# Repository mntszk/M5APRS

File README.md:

# M5APRS

M5Stack Basic GPS APRS tracker/receiver (1200bps AFSK)

[English](README.en.md) | 日本語

M5Stack Basic V2.6 で、GPS の位置を APRS パケットにして 1200bps AFSK で無線機へ送り、無線機で受信した APRS をデコードして画面に表示するアマチュア無線用のソフトです。個人の趣味のプロジェクトで、M5Stack 社とは関係ありません。

## かんたん書き込み (ビルド済みファイル)
Arduino IDE がなくても、ブラウザだけで書き込めます。

1. [Releases](https://github.com/mntszk/M5APRS/releases) から、最新の版の `M5APRS-x.y.z.bin` をダウンロードする (`x.y.z` は版の番号)
2. M5Stack Basic を USB ケーブルでパソコンにつなぐ
3. Chrome か Edge で、Espressif の書き込みツール [ESP Tool (esptool-js)](https://espressif.github.io/esptool-js/) を開く
4. 「Program」の欄で Baudrate を `921600` にして「Connect」を押し、出てきた一覧から M5Stack のポートを選ぶ
5. 「Flash Address」を **`0x0`** にして、1 のファイルを選び、「Program」を押す
6. 書き込みが終わったら、M5Stack のリセット (電源) ボタンを押して起動する
7. 続いて、下の「[使い方](#使い方)」の 4 (microSD の config.txt) に進む

- ポートが一覧に出ないときは、USB 変換チップのドライバー (M5Stack Basic V2.6 は CH9102) を入れてください
- 「Erase Flash」は押さないでください。押すと、本体に保存した設定 (シンボル、SSID、音量など) も消えます。押さなければ、版を上げても設定は残ります
- コマンドで書き込む場合: `esptool.py --chip esp32 --port <ポート> --baud 921600 write_flash 0x0 M5APRS-x.y.z.bin`

## 主な機能
- GPS (NMEA) の位置から、APRS の位置レポート (非圧縮形式) を作って送信 (A長押しで1パケット、または自動送信)
- ビーコンの自動送信: オフ / Ackのみ / 1〜60分ごと / フレックス (設定メニューで選択。電源を切っても保持)。他局の送信中は止むまで待つ
- フレックス: 速度と曲がり方で送信の間隔を変える。八重洲・ケンウッドの無線機のスマートビーコニングと同じ方式・同じ項目で、値は config.txt に書く
- 送信時に PTT を自動で ON/OFF (GPIO5 → トランジスタ)。PTT の最大時間は 10 秒
- 1200bps AFSK (Bell 202) の受信・デコード。非圧縮形式、圧縮形式、Mic-E の位置や、メッセージなどを受信一覧に表示
- メッセージ: 自分宛てのメッセージと一斉通知の受信、Ackの自動返送、メッセージの送信 (Ackが来るまで送り直し)。宛先は受信した局から、本文は定型文から選ぶ。CardKB2 をつなげば文字も入力できる
- 受信音: パケット・自局の折り返し・Ack・メッセージで音を分けて鳴らす (音量はモニター音とは別に設定)
- 記録の消去: 受信一覧・WX局・メッセージ・レーダーの局を、設定メニューから一覧ごと (またはすべて) 消せる (確認つき)
- WX(気象)画面: 気象データを含むパケットを受信した局 (最大8局) の気温・湿度・気圧・風・雨量を一覧と詳細で表示
- 受信状態の画面: 信号あり / データ受信中 / 受信OK / CRC不良、入力レベル、MARK/SPACE のトーン強度と比 (直近に受けた局の比も)、受信OK・CRC不良・雑音の件数
- 位置の取得元を手動で選択: GPS / 最後の位置 / 固定位置 (config.txt に最大8件)
- 送信音のモニター (内蔵スピーカー、5段階)
- 調整トーン: 設定メニューから、PTT付きで連続トーン (1200Hz / 2200Hz / 交互) を出して、減衰回路や送信レベルを調整できる (ダミーロード前提)
- シリアルモニタ (115200bps) への診断出力: PTTのタイミング、送受信パケット、受信の状態、定期の状態
- microSD に受信ログ (CSV) と動作ログを保存
- コールサインなど局ごとの設定は microSD の `config.txt` に書く (ビルドのときに書き換えるファイルはない)
- シンボル (21種類) と SSID (0〜15) を別々に設定。受信一覧・詳細・自局画面にシンボルのアイコンを表示
- レーダー画面: 自局を中心に、受信した局をシンボルのアイコンとコールサインで表示 (距離 1〜100km・自動、時間 10分〜24時間を切り替え)
- 画面の表示を日本語 / English で切り替え (設定メニューの「言語 / Language」)
- バージョン情報: 設定メニューの最後の項目で、バージョン (`version.h`)・ビルド日時・対応基板の版を表示

## 構成 (ハードウェア)
| 項目 | 内容 |
|---|---|
| 本体 | M5Stack Basic V2.6 |
| GPS | M5Stack 用 GPS モジュール (UART2: RX=GPIO16, TX=GPIO17, 115200bps) |
| 送信 | DAC GPIO26 → 減衰回路 → 無線機のマイク端子 |
| モニター | DAC GPIO25 (内蔵スピーカー) |
| PTT | GPIO5 → LED (PTT 表示を兼ねる) + 抵抗 → NPN トランジスタ (IF v1 は 2SC2712)。マイク線を抵抗を通して GND に落とす |
| 受信 | 無線機のイヤホン端子 → ADC GPIO36 (直流バイアス付き) |
| 記録 | 内蔵 microSD (CS=GPIO4) |

減衰回路、受信の入力回路、PTT 回路は外付けの基板です。IF v1 基板の設計データ (回路図、基板、部品表、ガーバー) は `hardware/` にあります。無線機はアナログ FM で使います。動作を確認した無線機は「現状」と `hardware/radio_compat.md` を参照してください。

> 注意: DAC の出力は約 2.6Vpp あるため、無線機のマイク入力へは必ず減衰させてください。PTT 線に GPIO を直結しないでください。

## 使い方
1〜3 は Arduino IDE でビルドして書き込む場合です。ビルド済みのファイルを書き込んだ場合は 4 から始めてください (「[かんたん書き込み](#かんたん書き込み-ビルド済みファイル)」)。

1. Arduino IDE に **M5Stack のボードパッケージ 2.x** (動作確認は 2.1.4) と、ライブラリ **M5Unified** を入れる
   - 「ツール」→「ボード」→「ボードマネージャ」で「M5Stack」を探し、版の欄で **2.1.4** を選んでインストールする
   - **3.x は未対応**です (ビルドすると「board package 3.x is not supported」と出て止まります)。3.x が入っているときも、同じ画面で 2.1.4 を選べば入れ替わります
2. ソースを **`M5APRS` という名前のフォルダ**に置く (Arduino IDE はスケッチ名とフォルダ名が同じである必要がある)
   - Releases や「Code」→「Download ZIP」の zip を展開すると、フォルダ名が `M5APRS-0.14.1` や `M5APRS-main` になります。**フォルダ名を `M5APRS` に変えてから** `M5APRS.ino` を開いてください
   - 名前を変えずに開くと、IDE が「M5APRS フォルダを作って移動しますか」と聞いてきます。ここで「はい」を押すと `M5APRS.ino` だけが移されて、`app_config.h: No such file or directory` などのエラーになります
3. `M5APRS.ino` を開き、ボード「M5Stack-Core-ESP32」などを選んで書き込む (書き換えるファイルはありません)
4. microSD カード (FAT32 でフォーマットしたもの。32GB 以下の SDHC など) を入れて起動すると、`/aprs/config.txt` (見本) ができるので、パソコンで開いて書き換え、カードを戻して再起動する
   ```
   callsign = N0CALL
   comment  = M5Stack APRS
   fixed1   = Home, 35.68123, 139.76712, 12
   ```
   最低限 `callsign` を自分のコールサインに書き換える (SSID は本体の設定メニューで選ぶ)。`NOCALL` のままでは送信しません

### 設定ファイル config.txt
- 1行に1つ「キー = 値」で書きます。行の先頭が `#` の行はコメントです (値の途中の `#` は文字として扱います)
- 書けるのは、コールサイン、コメント、固定位置 (8件)、デジパスの候補 (3つ)、メッセージの定型文と宛先の候補 (各8件)、送信レベル・PTT のタイミングなど無線機に合わせる値です。項目の一覧は `docs/APRS_M5Stack_spec.md` の 3.1 と、見本のファイルのコメントにあります
- 読むのは起動時だけです。書き間違いのある行は無視され、起動時の画面と、設定メニューの「バージョン情報」に行番号が出ます
- 読めた内容は本体にも控えておくので、microSD を抜いても前回の設定で動きます (SD に config.txt が無いときは、控えから書き戻します)
- 書き換えたあと、そのカードをそのまま他の人に渡すとコールサインも渡るので注意してください

## 操作
| ボタン | 短押し | 長押し |
|---|---|---|
| A | 前 (前の画面・項目) | **ビーコン送信** |
| B | 決定 (開く・変更・開始) | 戻る (1つ上へ) |
| C | 次 (次の画面・項目) | 設定メニュー (開く・閉じる) |

短押しはその画面の中の操作、長押しはどの画面でも同じ働きです。

受信一覧・WX局・メッセージ・レーダーの局はmicroSDに保存され、電源を入れ直しても残ります (送り直しの途中だったメッセージは「応答なし」になります)。

画面の下には、ボタンごとの働きを枠で囲んで出します (上段=短押し、下段=長押し)。画面上端の右側には、電池・SDカード・音量・受信音・GPS/位置・自動送信・送受信・未読メッセージの状態をアイコンで出します。

画面は 自局 / 受信一覧 / レーダー / メッセージ / WX / 受信状態 / 送信・設定 の7つです。設定メニューでは、位置の曖昧化、デジパス、シンボル、SSID、進行方向・速度、高度、モニター音量、受信音の音量、画面の明るさ、位置の取得元、表示の言語などを変えられ、記録の消去もできます。詳しくは `docs/` を参照してください。

## テスト
計算部分 (AFSK、AX.25/APRS、NMEA、設定、ログ、画面の組み立てなど) は、ESP32 なしでパソコン上でテストできます (g++ が必要)。
```
./tests/run_tests.sh          # 初期値の設定でテスト
./tests/run_tests.sh fixed    # 固定位置を設定した状態でテスト
```
実機でのタイミング、DAC/ADC の特性、外付け回路は、実機で確認する必要があります。

## 現状
ICOM ID-31 / ID-52、スタンダード C601 / C701 と IF v1 基板の組み合わせで動作を確認しています。config.txt の送信レベルなどの初期値は、この組み合わせで確かめた値です。

## ドキュメント
- `CHANGELOG.md` : 版ごとの変更 (日本語・英語)
- `docs/APRS_M5Stack_spec.md` : 仕様書
- `docs/UI_button_spec.xlsx` : ボタン割り当て、画面一覧、設定メニュー、シンボルと SSID、英語表示の対訳の表
- `hardware/` : IF v1 基板の設計データ (KiCad、ガーバー、部品表) と、無線機との相性の記録 (`radio_compat.md`)

## 注意
- アマチュア無線の免許と、運用ルールの範囲で使用してください。使用は自己責任です
- 想定運用周波数は 430MHz 帯の 1200bps AFSK 用の周波数です。無線機側で設定します

## 使用ライブラリ
- [M5Unified](https://github.com/m5stack/M5Unified) / [M5GFX](https://github.com/m5stack/M5GFX) (MIT)。日本語フォントは M5GFX に含まれる IPAex ゴシックの変換版 (IPA フォントライセンス)
- ESP32 Arduino core (LGPL 2.1)
- 機種名の表 (Mic-E、宛先 TOCALL) は [aprs-deviceid](https://github.com/aprsorg/aprs-deviceid) のデータ (CC BY-SA 2.0)

一覧と各ライセンスの条件は `THIRD_PARTY_LICENSES.md` にあります。

## ライセンス
Copyright (c) 2026 Minato Suzuki

- ソフトウェア (ファームウェア): [MIT ライセンス](LICENSE)
- インターフェース基板の設計データ (`hardware/`): [CERN-OHL-P v2](hardware/LICENSE) (寛容型のオープンハードウェア・ライセンス。詳しくは `hardware/README.md`)

- M5APRS のコードは、すべて独自に書いたものです。上の「使用ライブラリ」以外の、他のプロジェクトのソースは使っていません
- ただし、機種名の表 (`packet_parse.cpp` の `MICE_DEV` と `tocalls_table.h`) だけは aprs-deviceid のデータにもとづくもので、CC BY-SA 2.0 です
- ビルド済みのファイルを配るときは、`LICENSE` と `THIRD_PARTY_LICENSES.md` を添えてください

お願い (ライセンスの条件ではありません):
- 改造したものを配るときは、M5APRS とは別の名前にしてください
- 改造したものは、M5APRS 用の送信先コールサイン (TOCALL `APM5AP`) を使わず、それぞれで用意してください (aprs-deviceid に申請できます)

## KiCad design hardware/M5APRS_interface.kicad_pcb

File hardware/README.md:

# M5APRS interface board (IF v1)

M5Stack Basic と無線機 (マイク・スピーカー端子) をつなぐインターフェース基板の設計データです。

| File | 内容 |
|---|---|
| `M5APRS_interface.kicad_pro` / `.kicad_sch` / `.kicad_pcb` | KiCad のプロジェクト、回路図、基板 |
| `M5APRS_interface.svg` | 回路図 (画像) |
| `M5APRS_interface_BOM.csv` | 部品表 |
| `gerber/M5APRS_interface_1.zip` | 製造用データ (ガーバー・ドリル) |
| `fabrication-toolkit-options.json` | 製造データ出力の設定 |
| `radio_compat.md` | 無線機との相性の記録 |

## License / ライセンス

Copyright (c) 2026 Minato Suzuki

SPDX-License-Identifier: CERN-OHL-P-2.0

The hardware design files in this directory are licensed under the
CERN Open Hardware Licence Version 2 - Permissive (CERN-OHL-P v2).
See `LICENSE` in this directory, or https://ohwr.org/cern_ohl_p_v2.txt

You may redistribute and modify this source and make products using it
under the terms of the CERN-OHL-P v2. This source is distributed WITHOUT
ANY EXPRESS OR IMPLIED WARRANTY, INCLUDING OF MERCHANTABILITY, SATISFACTORY
QUALITY AND FITNESS FOR A PARTICULAR PURPOSE. Please see the CERN-OHL-P v2
for applicable conditions.

このディレクトリの基板の設計データは CERN-OHL-P v2 (寛容型のオープンハードウェア・ライセンス) です。
表示 (著作権・ライセンス・改変の記録) を残せば、自由に使用・改変・再配布でき、基板を作って配ったり売ったりもできます。
改変したデータを配るときは、改変したことを、日付と簡単な内容とともに書き添えてください (CERN-OHL-P v2 の 3.3)。
保証はありません。無線機への接続は自己責任で行ってください。

ファームウェア (このリポジトリのソフトウェア) は MIT ライセンスです (リポジトリ直下の `LICENSE`)。

### Third-party parts of the design / 設計に含まれる他の部品
- KiCad の標準ライブラリのシンボル・フットプリント (CC BY-SA 4.0。KiCad ライブラリの例外条項により、これらを使った設計にはその条件は及ばない)
- RV1・RV2 (Bourns 3362P) のフットプリント `TRIM_3362P-1-102LF` は SnapMagic (旧 SnapEDA) のもの。同社の利用規約 (Design License) に基づき、基板の設計データに組み込んで配布している。このフットプリント単体は CERN-OHL-P v2 の対象外で、設計データから取り出して単体で配布することはできない。単体で必要なときは SnapMagic から入手してほしい
  / The footprint `TRIM_3362P-1-102LF` of RV1 and RV2 (Bourns 3362P) is from SnapMagic (formerly SnapEDA). It is included in this board design under the SnapMagic Design License. The footprint by itself is not covered by the CERN-OHL-P v2 and must not be extracted from the design and distributed on its own. Get it from SnapMagic if you need it separately.

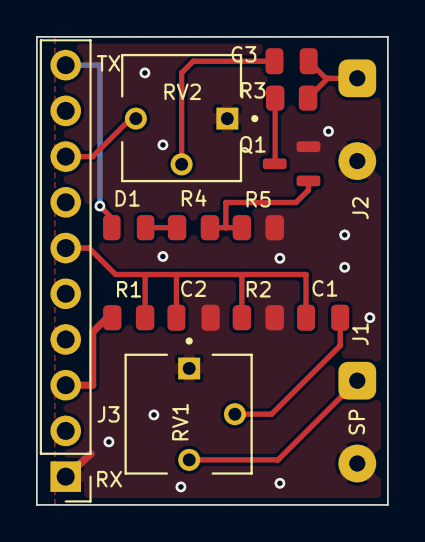
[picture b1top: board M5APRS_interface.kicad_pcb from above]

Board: 2 copper layers, 19.5 x 26.0 mm, 15 parts (0 on the bottom side), 12 nets.

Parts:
C1, C3: 10u; C_0805_2012Metric
C2: 0.01u; C_0805_2012Metric
D1: LED; LED_0805_2012Metric
J1: SP; SolderWire-0.5sqmm_1x02_P4.6mm_D0.9mm_OD2.1mm
J2: MIC; SolderWire-0.5sqmm_1x02_P4.6mm_D0.9mm_OD2.1mm
J3: M5_Side_6-15; PinHeader_1x10_P2.54mm_Vertical
Q1: 2SC2712; SOT-23
R1, R2: 47k; R_0805_2012Metric
R3: 2k; R_0805_2012Metric
R4: 1.2k; R_0805_2012Metric
R5: 10k; R_0805_2012Metric
RV1: 5k; TRIM_3362P-1-102LF
RV2: 1k; TRIM_3362P-1-102LF

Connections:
+3V3: J3.3, R1.1
/G5_PTT: D1.2 (A), J3.10
/G26_DAC: J3.8, RV2.3
/G36_ADC: C1.2, C2.1, J3.6, R1.2, R2.1
GND: C2.2, J1.2, J2.2, J3.1, Q1.2 (E), R2.2, R5.2, RV1.1, RV2.1
unnamed: C1.1, RV1.2
unnamed: C3.2, RV2.2
unnamed: D1.1 (K), R4.2
unnamed: J1.1, RV1.3
unnamed: C3.1, J2.1, R3.1
unnamed: Q1.1 (B), R4.1, R5.1
unnamed: Q1.3 (C), R3.2

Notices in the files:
hardware/M5APRS_interface.kicad_pcb:
License: CERN-OHL-P-2.0
